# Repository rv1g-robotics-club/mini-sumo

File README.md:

# RV1G Mini Sumo year 2026 version

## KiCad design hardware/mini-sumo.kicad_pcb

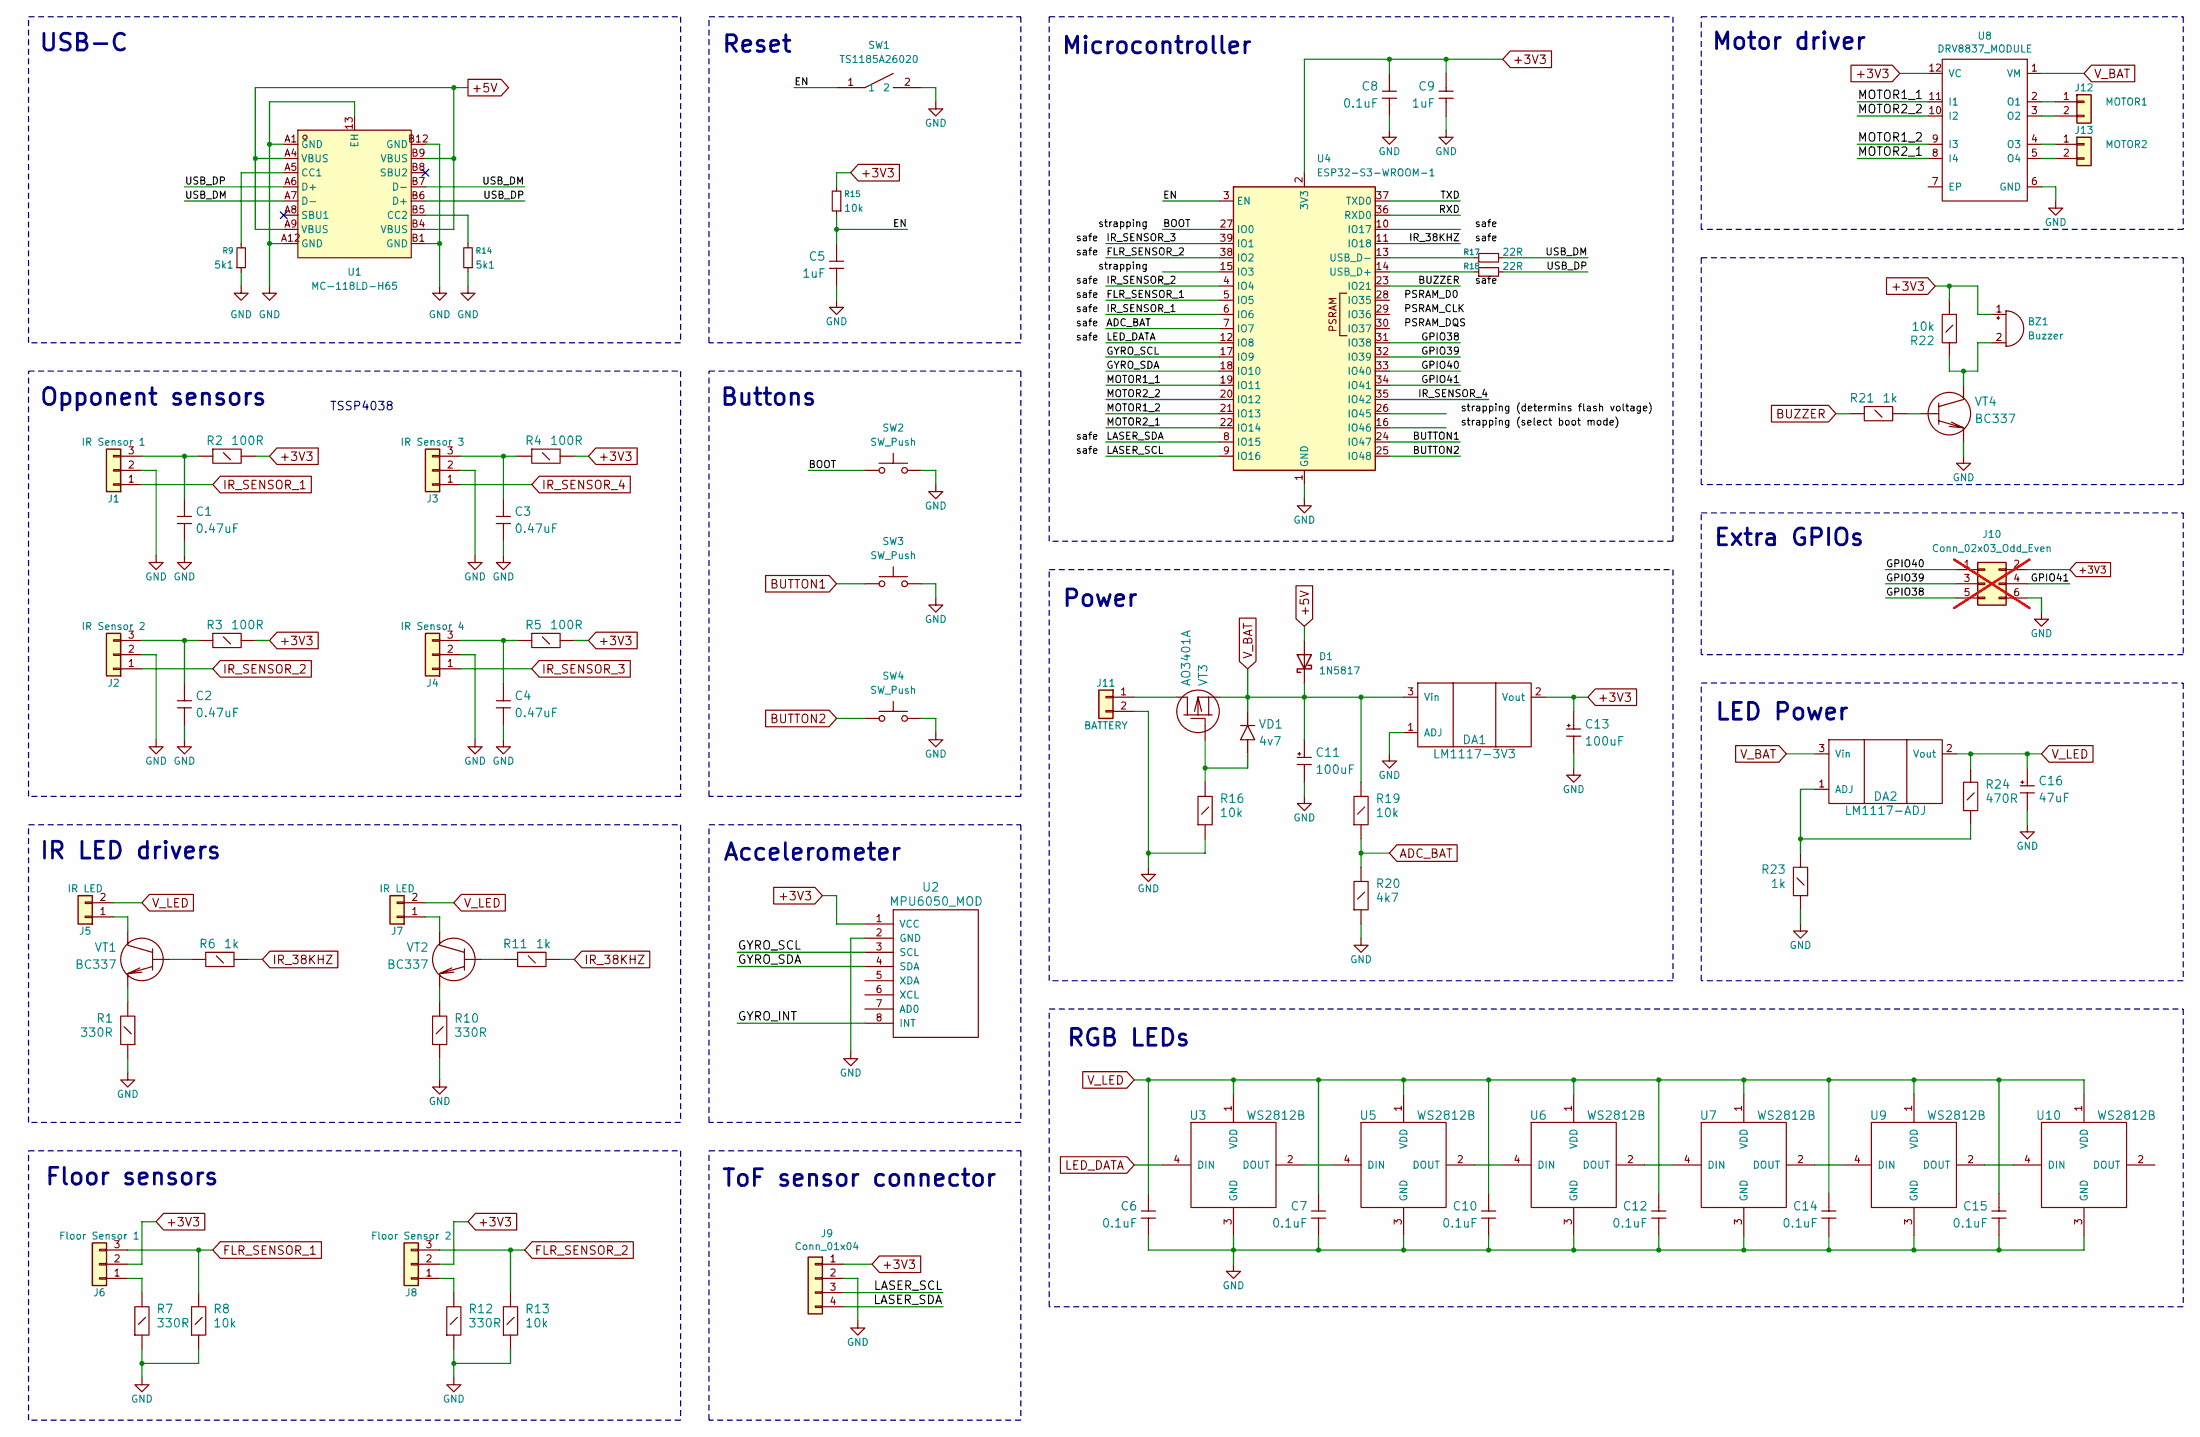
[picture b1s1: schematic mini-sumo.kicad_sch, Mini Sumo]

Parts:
BZ1: Buzzer; Beeper_12xx; LCSC Part C2693577
C1, C2, C3, C4: 0.47uF; C-5mm; LCSC Part C5632433
C5, C9: 1uF; C_Disc_D3.0mm_W1.6mm_P2.50mm; LCSC Part C5632434
C6, C7, C8, C10, C12, C14, C15: 0.1uF; C_Disc_D3.0mm_W1.6mm_P2.50mm; LCSC Part C5632430
C11, C13: 100uF; CE63x25; LCSC Part C44588
C16: 47uF; CE63x25; LCSC Part C13654
D1: 1N5817; D_DO-41_SOD81_P2.54mm_Vertical_KathodeUp; LCSC Part C7544876
DA1: LM1117-3V3; SOT-223; LCSC Part C347222
DA2: LM1117-ADJ; SOT-223; LCSC Part C347224
J1: IR Sensor 1; JST-B3B-ZR; LCSC Part C722936
J2: IR Sensor 2; JST-B3B-ZR; LCSC Part C722936
J3: IR Sensor 3; JST-B3B-ZR; LCSC Part C722936
J4: IR Sensor 4; JST-B3B-ZR; LCSC Part C722936
J5, J7: IR LED; JST-B2B-ZR; LCSC Part C722910
J6: Floor Sensor 1; JST-B3B-ZR; LCSC Part C722936
J8: Floor Sensor 2; JST-B3B-ZR; LCSC Part C722936
J9: Conn_01x04; JST-B4B-ZR; LCSC Part C722918
J10: Conn_02x03_Odd_Even; PinHeader_2x03_P2.54mm_Vertical; not fitted
J11: BATTERY; JST_PH_B2B-PH-K_1x02_P2.00mm_Vertical; LCSC Part C7429542
J12: MOTOR1; JST_PH_B2B-PH-K_1x02_P2.00mm_Vertical; LCSC Part C7429542
J13: MOTOR2; JST_PH_B2B-PH-K_1x02_P2.00mm_Vertical; LCSC Part C7429542
R1, R7, R10, R12: 330R; R_W8_THT_Hor_6mm; LCSC Part C119858
R2, R3, R4, R5: 100R; R_W8_THT_Hor_6mm; LCSC Part C2896920
R6, R11, R21, R23: 1k; R_W8_THT_Hor_6mm; LCSC Part C119870
R8, R13, R15, R19, R22: 10k; R_W8_THT_Hor_6mm; LCSC Part C714232
R9, R14: 5k1; R_W8_THT_Hor_6mm; LCSC Part C119195
R16: 10k; R_W8_THT_Vert; LCSC Part C714232
R17, R18: 22R; R_W8_THT_Hor_6mm; LCSC Part C119830
R20: 4k7; R_W8_THT_Hor_6mm; LCSC Part C714232
R24: 470R; R_W8_THT_Hor_6mm; LCSC Part C119862
SW1: TS1185A26020; SW-SMD_TS1185A26020; LCSC Part C22375376
SW2, SW3, SW4: SW_Push; SW_PUSH_6mm_H5mm; LCSC Part C2845253
U1: MC-118LD-H65; USB-C-TH_HANBO_MC-118LD-H65; LCSC Part C6332304
U2: MPU6050_MOD; MPU6050
U3, U5, U6, U7, U9, U10: WS2812B; LCSC Part C2843785
U4: ESP32-S3-WROOM-1
U8: DRV8837_MODULE
VD1: 4v7; D_DO-35_SOD27_P2.54mm_Vertical_AnodeUp; LCSC Part C5158978
VT1, VT2, VT4: BC337; TO-92_Inline; LCSC Part C713610
VT3: AO3401A; SOT-23; LCSC Part C15127

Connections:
+3V3: BZ1.1 (+), C8.1, C9.1, C13.1, DA1.2 (Vout), J6.2, J8.2, J9.1, J10.2, R2.2, R3.2, R4.2, R5.2, R15.2, R22.1, U2.1 (VCC), U4.2 (3V3), U8.12 (VC)
+5V: D1.2 (A), U1.A4 (VBUS), U1.A9 (VBUS), U1.B4 (VBUS), U1.B9 (VBUS)
/BOOT: SW2.1, U4.27 (IO0)
/EN: C5.1, R15.1, SW1.1, U4.3 (EN)
/GPIO38: J10.5, U4.31 (IO38)
/GPIO39: J10.3, U4.32 (IO39)
/GPIO40: J10.1, U4.33 (IO40)
/GPIO41: J10.4, U4.34 (IO41)
/GYRO_INT: U2.8 (INT)
/GYRO_SCL: U2.3 (SCL), U4.17 (IO9)
/GYRO_SDA: U2.4 (SDA), U4.18 (IO10)
/LASER_SCL: J9.3, U4.9 (IO16)
/LASER_SDA: J9.4, U4.8 (IO15)
/MOTOR1_1: U4.19 (IO11), U8.11 (I1)
/MOTOR1_2: U4.21 (IO13), U8.9 (I3)
/MOTOR2_1: U4.22 (IO14), U8.8 (I4)
/MOTOR2_2: U4.20 (IO12), U8.10 (I2)
/RXD: U4.36 (RXD0)
/TXD: U4.37 (TXD0)
/USB_DM: R17.2, U1.A7 (D-), U1.B7 (D-)
/USB_DP: R18.2, U1.A6 (D+), U1.B6 (D+)
ADC_BAT: R19.1, R20.2, U4.7 (IO7)
BUTTON1: SW3.1, U4.24 (IO47)
BUTTON2: SW4.1, U4.25 (IO48)
BUZZER: R21.1, U4.23 (IO21)
FLR_SENSOR_1: J6.3, R8.2, U4.5 (IO5)
FLR_SENSOR_2: J8.3, R13.2, U4.38 (IO2)
GND: C1.2, C2.2, C3.2, C4.2, C5.2, C6.2, C7.2, C8.2, C9.2, C10.2, C11.2, C12.2, C13.2, C14.2, C15.2, C16.2, DA1.1 (ADJ), J1.2, J2.2, J3.2, J4.2, J9.2, J10.6, J11.2, R1.1, R7.1, R8.1, R9.1, R10.1, R12.1, R13.1, R14.1, R16.1, R20.1, R23.1, SW1.2, SW2.2, SW3.2, SW4.2, U1.13 (EH), U1.A1 (GND), U1.A12 (GND), U1.B1 (GND), U1.B12 (GND), U2.2 (GND), U3.3 (GND), U4.1 (GND), U4.40 (GND), U4.41 (GND), U5.3 (GND), U6.3 (GND), U7.3 (GND), U8.6 (GND), U9.3 (GND), U10.3 (GND), VT4.3 (E)
IR_38KHZ: R6.2, R11.2, U4.11 (IO18)
IR_SENSOR_1: J1.1, U4.6 (IO6)
IR_SENSOR_2: J2.1, U4.4 (IO4)
IR_SENSOR_3: J4.1, U4.39 (IO1)
IR_SENSOR_4: J3.1, U4.35 (IO42)
LED_DATA: U3.4 (DIN), U4.12 (IO8)
unnamed: BZ1.2 (-), R22.2, VT4.1 (K)
unnamed: DA2.1 (ADJ), R23.2, R24.1
unnamed: C1.1, J1.3, R2.1
unnamed: C2.1, J2.3, R3.1
unnamed: C3.1, J3.3, R4.1
unnamed: C4.1, J4.3, R5.1
unnamed: J5.1, VT1.1 (K)
unnamed: J6.1, R7.2
unnamed: J7.1, VT2.1 (K)
unnamed: J8.1, R12.2
unnamed: J11.1, VT3.3 (D)
unnamed: J12.1, U8.2 (O1)
unnamed: J12.2, U8.3 (O2)
unnamed: J13.1, U8.4 (O3)
unnamed: J13.2, U8.5 (O4)
unnamed: R9.2, U1.A5 (CC1)
unnamed: R14.2, U1.B5 (CC2)
unnamed: U3.2 (DOUT), U5.4 (DIN)
unnamed: R18.1, U4.14 (USB_D+)
unnamed: R17.1, U4.13 (USB_D-)
unnamed: U5.2 (DOUT), U6.4 (DIN)
unnamed: U6.2 (DOUT), U7.4 (DIN)
unnamed: U7.2 (DOUT), U9.4 (DIN)
unnamed: U9.2 (DOUT), U10.4 (DIN)
unnamed: R16.2, VD1.1 (A), VT3.1 (G)
unnamed: R6.1, VT1.2 (B)
unnamed: R1.2, VT1.3 (E)
unnamed: R11.1, VT2.2 (B)
unnamed: R10.2, VT2.3 (E)
unnamed: R21.2, VT4.2 (B)
V_BAT: C11.1, D1.1 (K), DA1.3 (Vin), DA2.3 (Vin), R19.2, U8.1 (VM), VD1.2 (K), VT3.2 (S)
V_LED: C6.1, C7.1, C10.1, C12.1, C14.1, C15.1, C16.1, DA2.2 (Vout), J5.2, J7.2, R24.2, U3.1 (VDD), U5.1 (VDD), U6.1 (VDD), U7.1 (VDD), U9.1 (VDD), U10.1 (VDD)

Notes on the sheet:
Floor sensors
Reset
Microcontroller
RGB LEDs
Opponent sensors
Extra GPIOs
ToF sensor connector
Motor driver
Buttons
IR LED drivers
TSSP4038
USB-C
Power
LED Power
Accelerometer

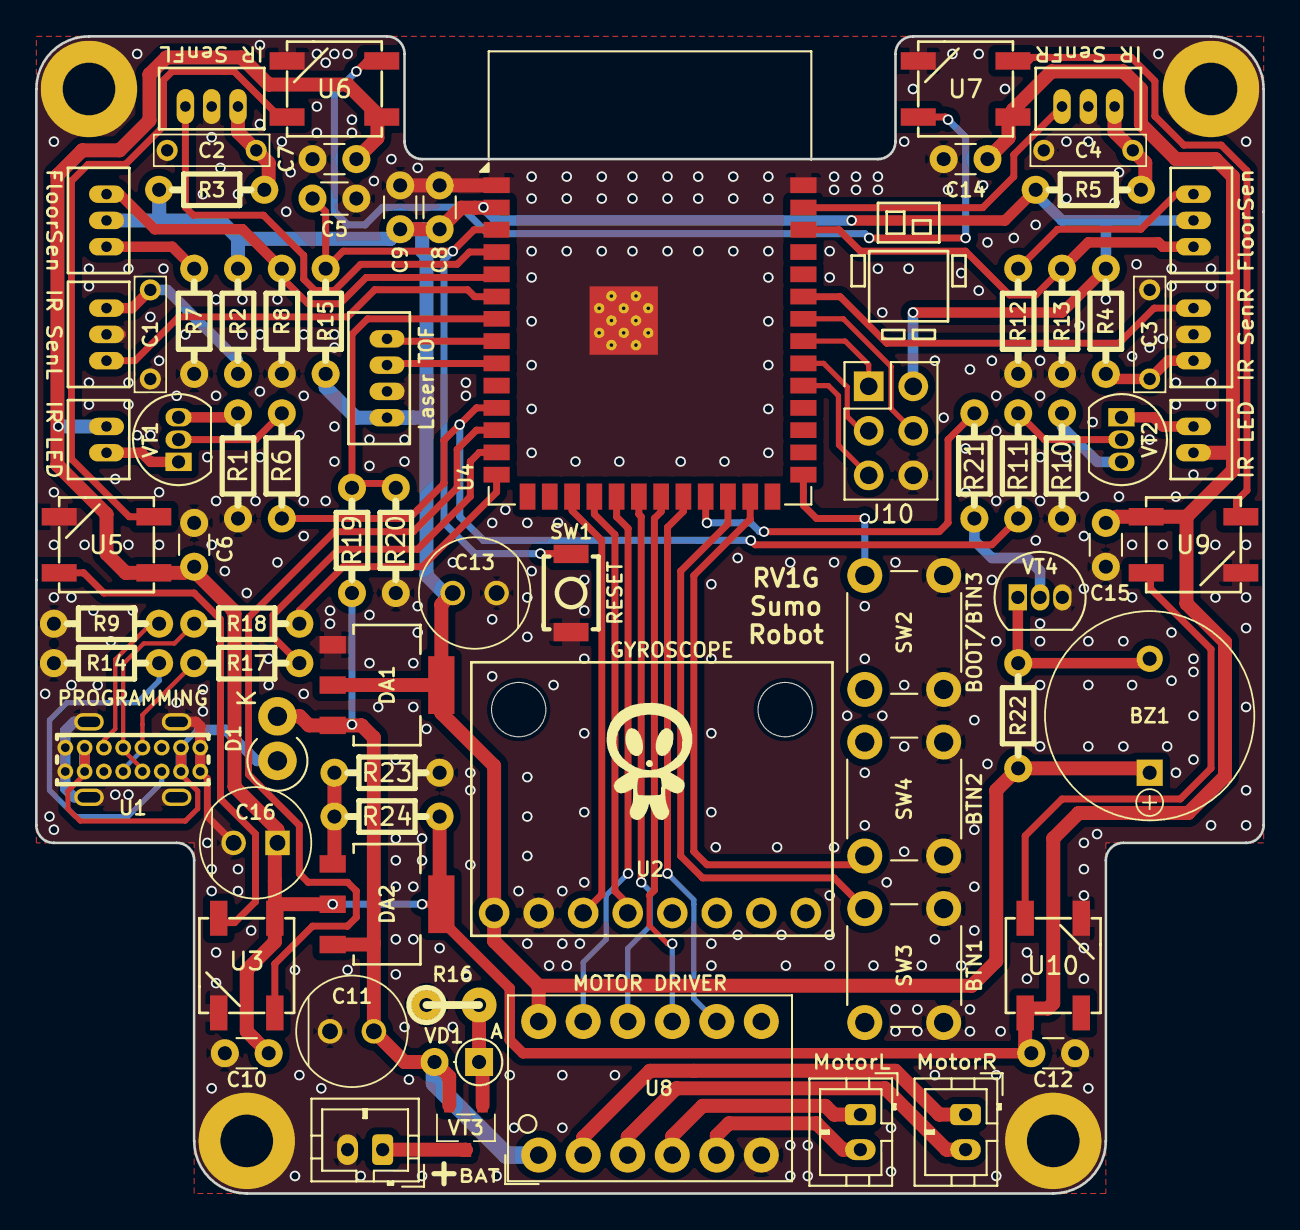
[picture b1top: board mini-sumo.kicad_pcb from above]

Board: 2 copper layers, 70.0 x 66.0 mm, 80 parts (0 on the bottom side), 63 nets.

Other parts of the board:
X**: 1PIN
X**#2, X**#3, X**#4: 1PIN

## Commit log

2026-01-06 Finalized the PCB
2026-01-06 Added GND vias
2026-01-06 Improved sikscreen on PCB. Changed reverse polarity transistor to AO3401A.
2026-01-25 Organized and fixed schematic. Added schematic PDF and HTML interactive BOM.
2026-05-11 Added firmware libraries
2026-05-11 Added robot.py
2026-05-11 Improved motion library
2026-05-11 Added Motion control library usage example
